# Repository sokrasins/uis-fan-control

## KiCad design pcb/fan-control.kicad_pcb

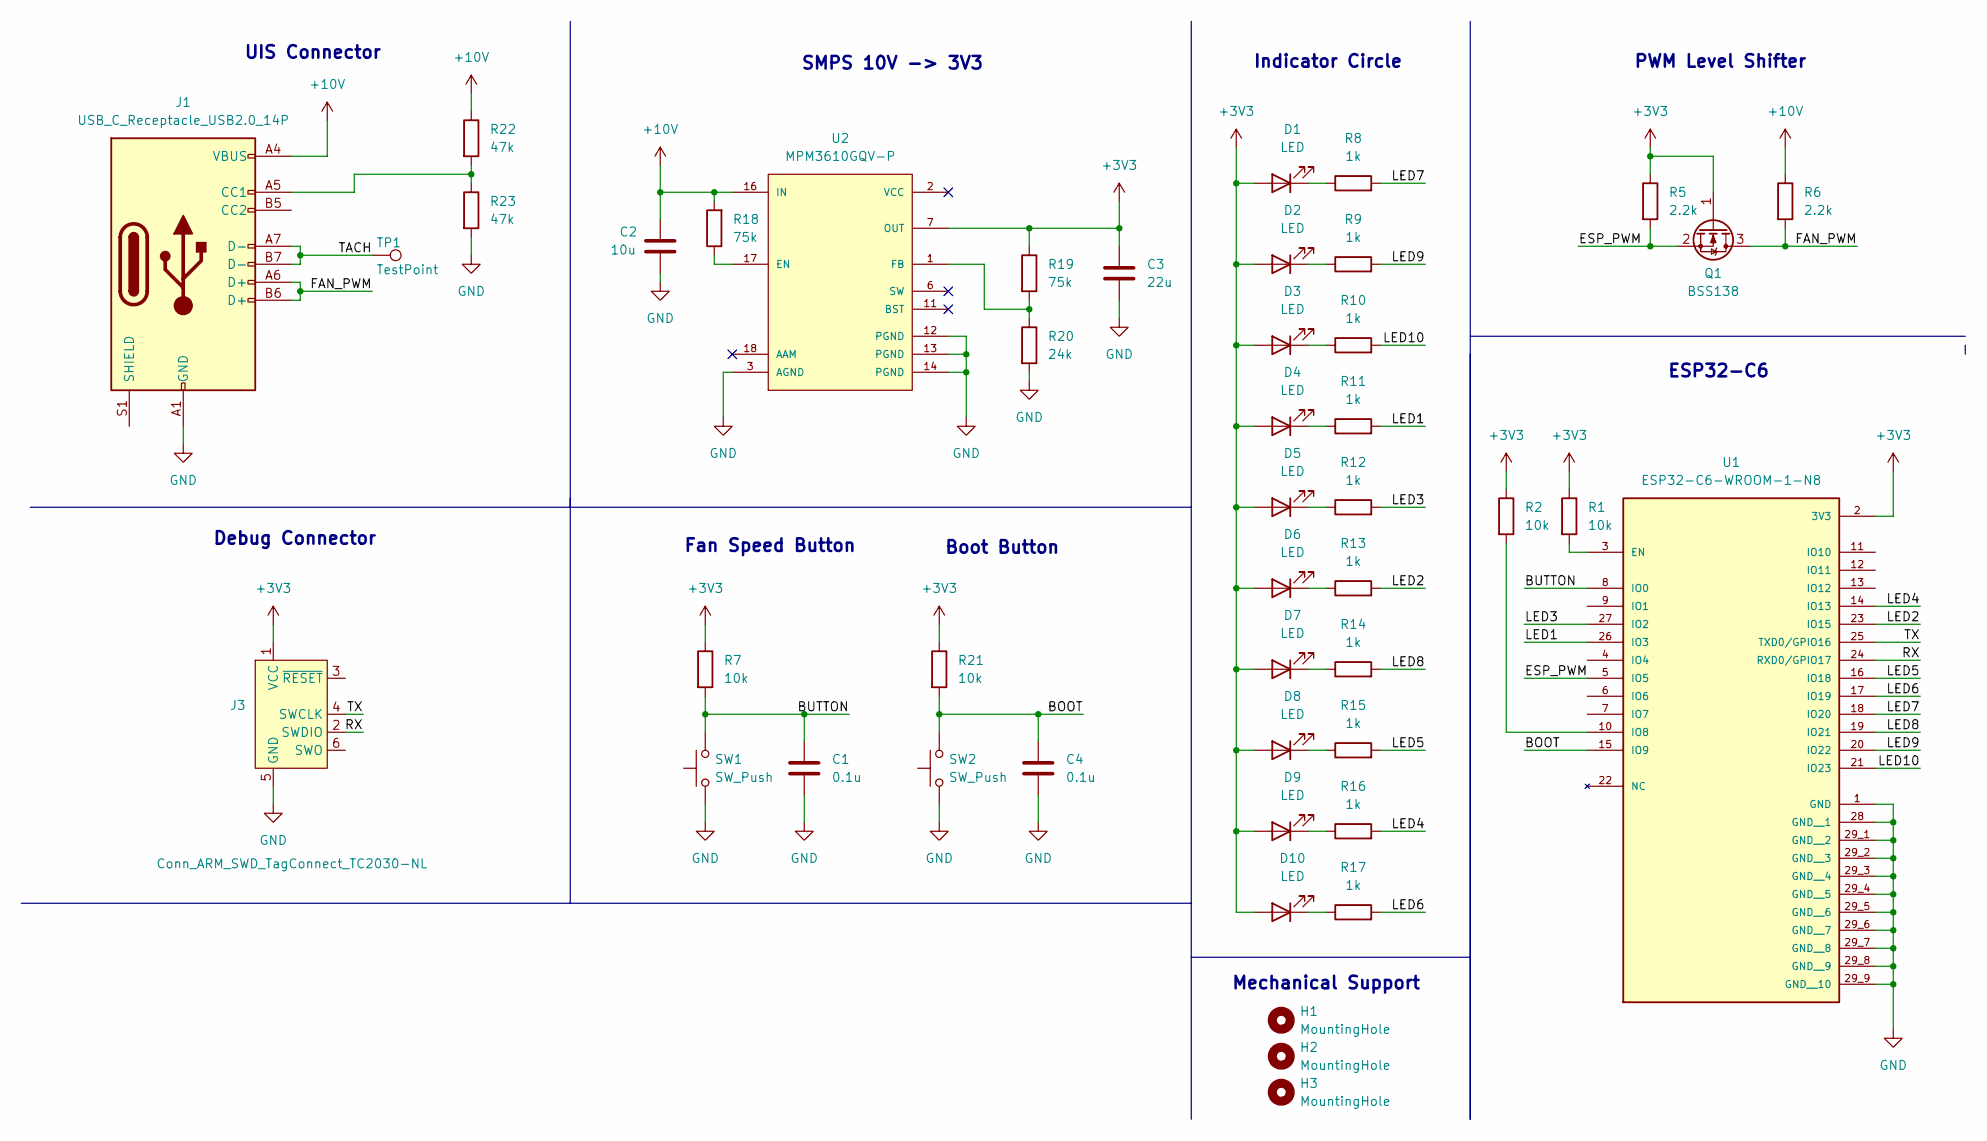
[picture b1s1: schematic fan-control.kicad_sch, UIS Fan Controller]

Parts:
C1, C4: 0.1u; C_0603_1608Metric_Pad1.08x0.95mm_HandSolder
C2: 10u; C_0805_2012Metric_Pad1.18x1.45mm_HandSolder
C3: 22u; C_0805_2012Metric_Pad1.18x1.45mm_HandSolder
D1, D2, D3, D4, D5, D6, D7, D8, D9, D10: LED; LED_0603_1608Metric_Pad1.05x0.95mm_HandSolder
H1, H2, H3: MountingHole; MountingHole_2.2mm_M2
J1: USB_C_Receptacle_USB2.0_14P; USB_C_Receptacle_GCT_USB4105-xx-A_16P_TopMnt_Horizontal
J3: Conn_ARM_SWD_TagConnect_TC2030-NL; Tag-Connect_TC2030-IDC-NL_2x03_P1.27mm_Vertical
Q1: BSS138; SOT-23
R1, R2, R7, R21: 10k; R_0603_1608Metric_Pad0.98x0.95mm_HandSolder
R5, R6: 2.2k; R_0603_1608Metric_Pad0.98x0.95mm_HandSolder
R8, R9, R10, R11, R12, R13, R14, R15, R16, R17: 1k; R_0603_1608Metric_Pad0.98x0.95mm_HandSolder
R18, R19: 75k; R_0603_1608Metric_Pad0.98x0.95mm_HandSolder
R20: 24k; R_0603_1608Metric_Pad0.98x0.95mm_HandSolder
R22, R23: 47k; R_0603_1608Metric_Pad0.98x0.95mm_HandSolder
SW1, SW2: SW_Push; 4P-3.4x3.4mm
TP1: TestPoint; TestPoint_Pad_1.5x1.5mm
U1: ESP32-C6-WROOM-1-N8; XCVR_ESP32-C6-WROOM-1-N8; PARTREV 1.0
U2: MPM3610GQV-P; CONV_MPM3610GQV-P; PARTREV 1.01

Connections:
+3V3: C3.1, D1.2 (A), D2.2 (A), D3.2 (A), D4.2 (A), D5.2 (A), D6.2 (A), D7.2 (A), D8.2 (A), D9.2 (A), D10.2 (A), J3.1 (VCC), Q1.1 (G), R1.1, R2.1, R5.1, R7.1, R19.1, R21.1, U1.2 (3V3), U2.7 (OUT)
+10V: C2.1, J1.A4 (VBUS), J1.A9 (VBUS), J1.B4 (VBUS), J1.B9 (VBUS), R6.1, R18.2, R22.1, U2.16 (IN)
/BOOT: C4.1, R21.2, SW2.2, U1.15 (IO9)
/BUTTON: C1.1, R7.2, SW1.2, U1.8 (IO0)
/ESP_PWM: Q1.2 (S), R5.2, U1.5 (IO5)
/FAN_PWM: J1.A6 (D+), J1.B6 (D+), Q1.3 (D), R6.2
/LED1: R11.2, U1.26 (IO3)
/LED2: R13.2, U1.23 (IO15)
/LED3: R12.2, U1.27 (IO2)
/LED4: R16.2, U1.14 (IO13)
/LED5: R15.2, U1.16 (IO18)
/LED6: R17.2, U1.17 (IO19)
/LED7: R8.2, U1.18 (IO20)
/LED8: R14.2, U1.19 (IO21)
/LED9: R9.2, U1.20 (IO22)
/LED10: R10.2, U1.21 (IO23)
/RX: J3.2 (SWDIO), U1.24 (RXD0/GPIO17)
/TACH: J1.A7 (D-), J1.B7 (D-), TP1.1
/TX: J3.4 (SWCLK), U1.25 (TXD0/GPIO16)
GND: C1.2, C2.2, C3.2, C4.2, J1.A1 (GND), J1.A12 (GND), J1.B1 (GND), J1.B12 (GND), J3.5 (GND), R20.2, R23.2, SW1.1, SW2.1, U1.1 (GND), U1.28 (GND__1), U1.29_1 (GND__2), U1.29_2 (GND__3), U1.29_3 (GND__4), U1.29_4 (GND__5), U1.29_5 (GND__6), U1.29_6 (GND__7), U1.29_7 (GND__8), U1.29_8 (GND__9), U1.29_9 (GND__10), U2.3 (AGND), U2.12 (PGND), U2.13 (PGND), U2.14 (PGND)
unnamed: D1.1 (K), R8.1
unnamed: D2.1 (K), R9.1
unnamed: D3.1 (K), R10.1
unnamed: D4.1 (K), R11.1
unnamed: D5.1 (K), R12.1
unnamed: D6.1 (K), R13.1
unnamed: D7.1 (K), R14.1
unnamed: D8.1 (K), R15.1
unnamed: D9.1 (K), R16.1
unnamed: D10.1 (K), R17.1
unnamed: J1.A5 (CC1), R22.2, R23.1
unnamed: R1.2, U1.3 (EN)
unnamed: R2.2, U1.10 (IO8)
unnamed: R18.1, U2.17 (EN)
unnamed: R19.2, R20.1, U2.1 (FB)

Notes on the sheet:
ESP32-C6
SMPS 10V -> 3V3
Indicator Circle
Mechanical Support
PWM Level Shifter
Boot Button
Fan Speed Button
Debug Connector
UIS Connector

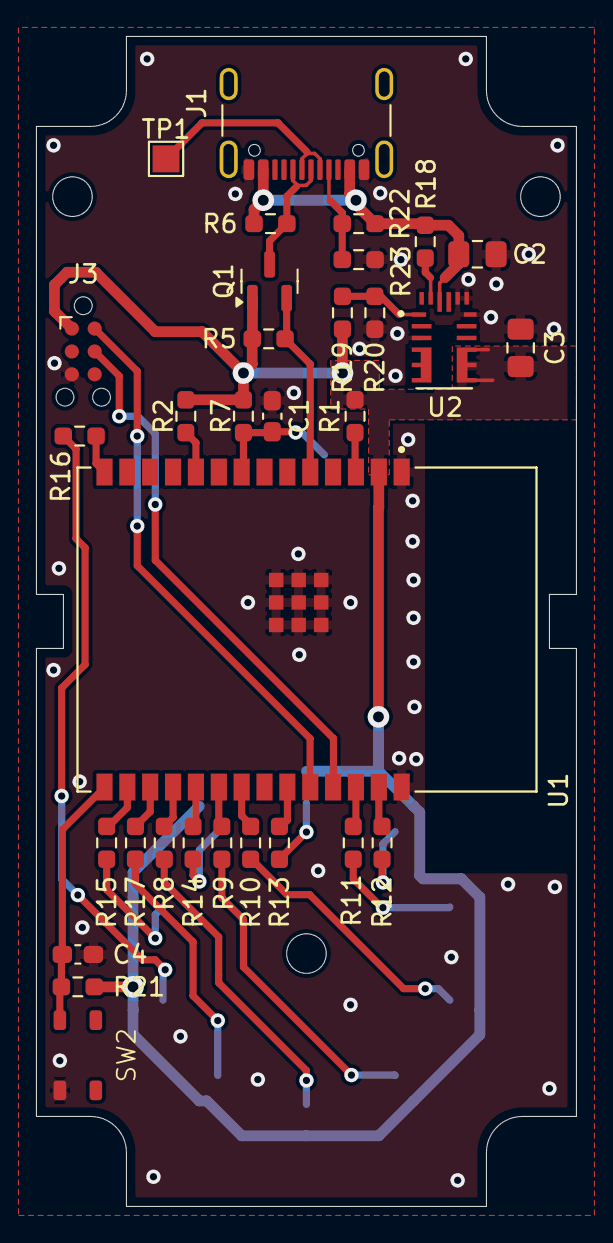
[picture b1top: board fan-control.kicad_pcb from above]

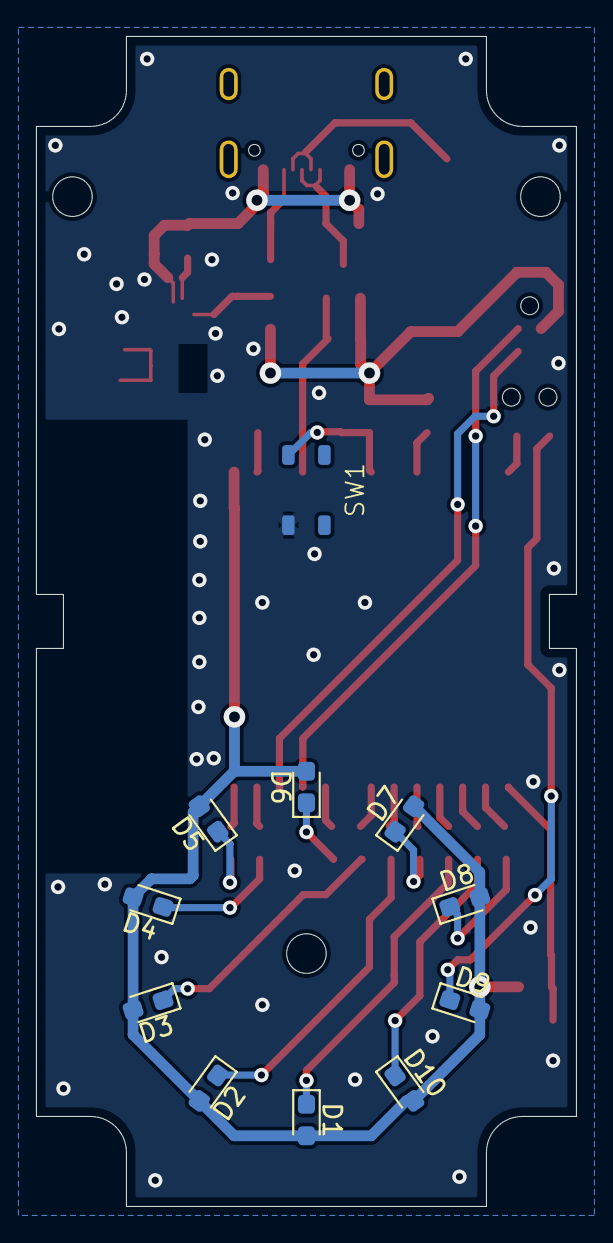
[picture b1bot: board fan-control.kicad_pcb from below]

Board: 2 copper layers, 30.0 x 65.0 mm, 46 parts (11 on the bottom side), 35 nets.

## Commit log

2025-03-13 schematic
2025-03-13 More sch
2025-03-14 Outline
2025-03-15 some layout
2025-03-15 Routing
2025-03-15 drc, nearing end of layout
2025-03-16 Added production files
2025-03-19 pwm steps
2025-03-20 fan and button
2025-03-20 clean up
2025-03-20 reorg
2025-03-20 Fix timer
2025-03-20 Set up logging
2025-03-21 CHange main around
2025-03-21 Fix button polarity
2025-03-21 Add NVS storage
2025-03-31 Add LED wheel in code
2025-03-31 wheel leds off by default
2026-02-21 Add switch comment
